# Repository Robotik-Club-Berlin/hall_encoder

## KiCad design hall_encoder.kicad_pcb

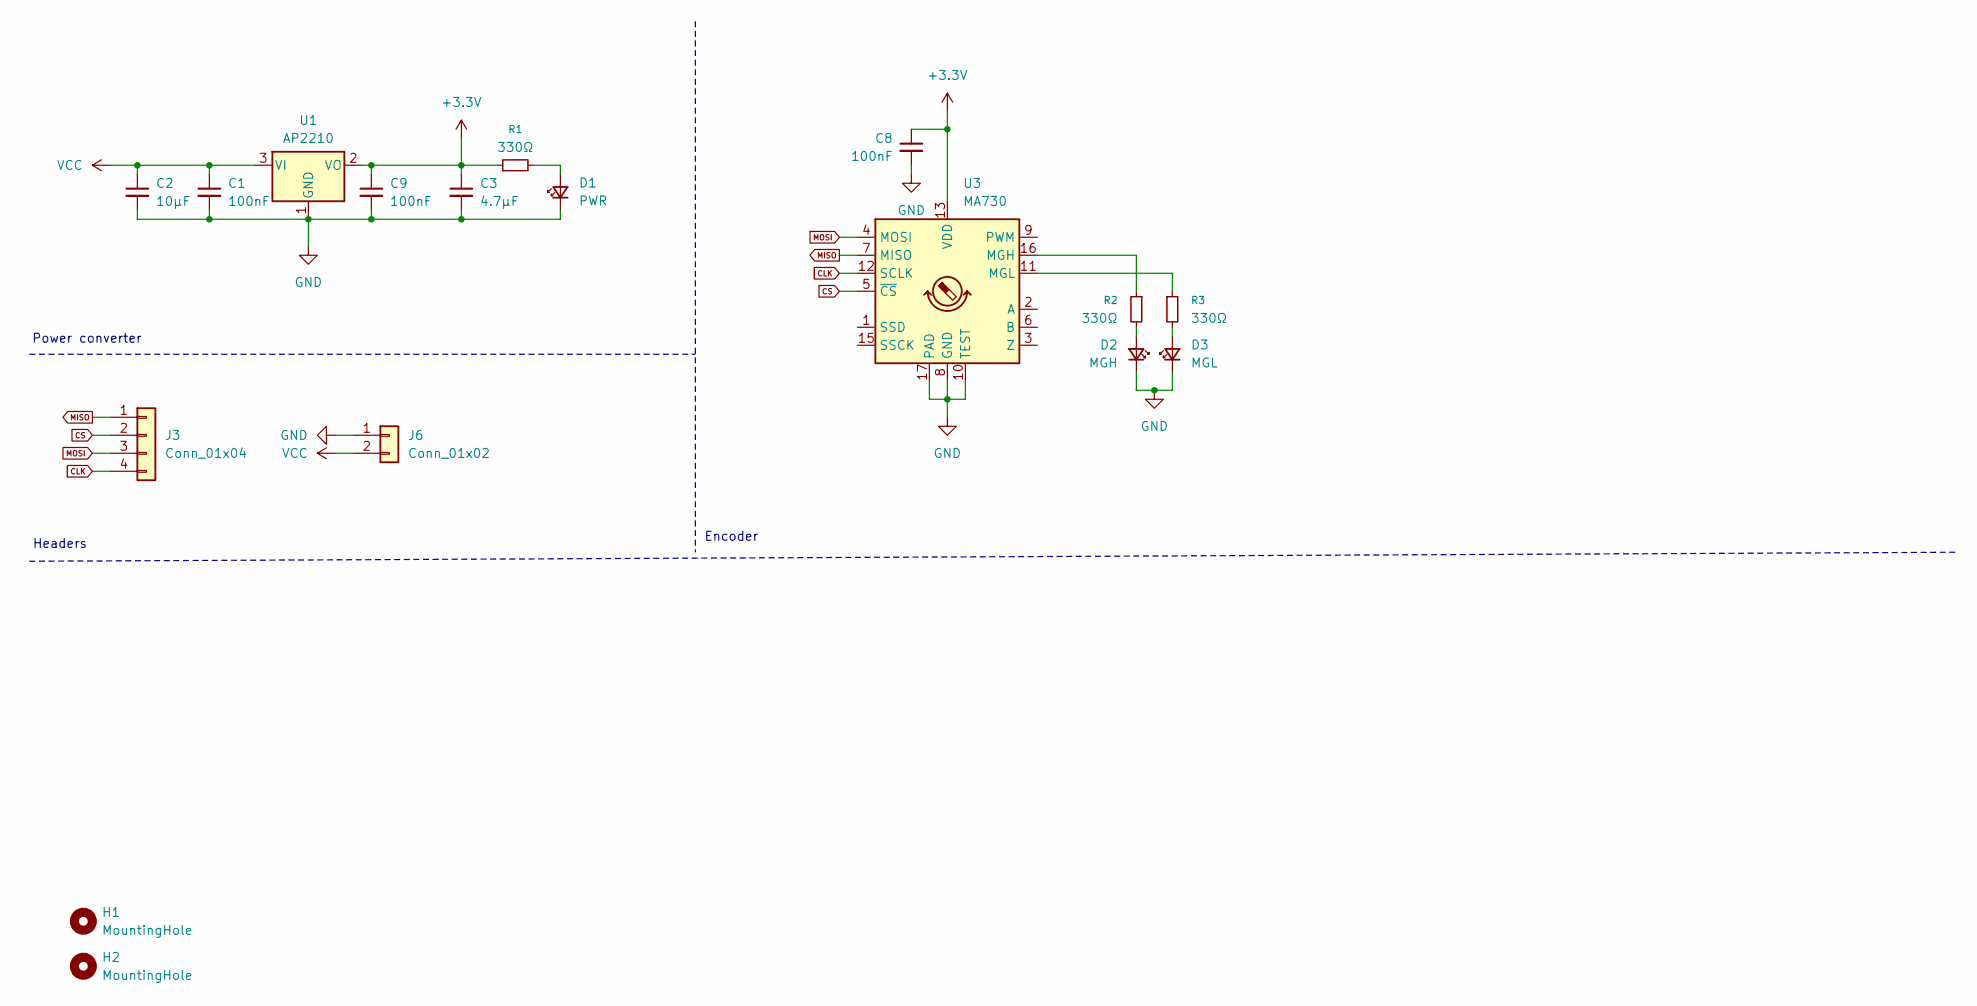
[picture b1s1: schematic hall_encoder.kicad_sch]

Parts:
C1, C8, C9: 100nF; C_0603_1608Metric_Pad1.08x0.95mm_HandSolder
C2: 10µF; C_1206_3216Metric_Pad1.33x1.80mm_HandSolder
C3: 4.7µF; C_0603_1608Metric_Pad1.08x0.95mm_HandSolder
D1: PWR; LED_0603_1608Metric_Pad1.05x0.95mm_HandSolder
D2: MGH; LED_0603_1608Metric_Pad1.05x0.95mm_HandSolder
D3: MGL; LED_0603_1608Metric_Pad1.05x0.95mm_HandSolder
H1, H2: MountingHole; MountingHole_2.2mm_M2
J3: Conn_01x04; PinHeader_1x04_P2.54mm_Vertical
J6: Conn_01x02; PinHeader_1x02_P2.54mm_Vertical
R1, R2, R3: 330Ω; R_0603_1608Metric_Pad0.98x0.95mm_HandSolder
U1: AP2210; SOT-23-3
U3: MA730; QFN-16-1EP_3x3mm_P0.5mm_EP1.75x1.75mm

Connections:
+3.3V: C3.1, C8.1, C9.1, R1.1, U1.2 (VO), U3.13 (VDD)
CLK: J3.4, U3.12 (SCLK)
CS: J3.2, U3.5 (~CS)
GND: C1.2, C2.2, C3.2, C8.2, C9.2, D1.1 (K), D2.1 (K), D3.1 (K), J6.1, U1.1 (GND), U3.8 (GND), U3.10 (TEST), U3.17 (PAD)
MISO: J3.1, U3.7 (MISO)
MOSI: J3.3, U3.4 (MOSI)
unnamed: D1.2 (A), R1.2
unnamed: D2.2 (A), R2.2
unnamed: D3.2 (A), R3.2
unnamed: R2.1, U3.16 (MGH)
unnamed: R3.1, U3.11 (MGL)
VCC: C1.1, C2.1, J6.2, U1.3 (VI)

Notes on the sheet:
Encoder
Headers
Power converter

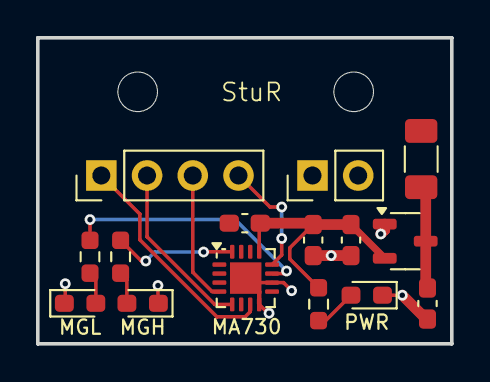
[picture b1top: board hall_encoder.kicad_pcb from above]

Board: 2 copper layers, 23.0 x 17.0 mm, 17 parts (0 on the bottom side), 12 nets.

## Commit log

2026-05-08 Add existing encoder
2026-05-08 Remove all can components
2026-05-11 Reference step file
